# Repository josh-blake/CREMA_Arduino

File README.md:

CREMA
=====

ControlleR for Espresso MAchines (http://josh.to/crema)

This entire project (including hardware and software) is distrubuted under the Creative Commons Attribution-NonCommercial-ShareAlike 3.0 Unported License.
http://creativecommons.org/licenses/by-nc-sa/3.0/deed.en_US

Please contact crema at josh dot to if you have any specific questions or would like to contribute to this project.

Enjoy the espresso.

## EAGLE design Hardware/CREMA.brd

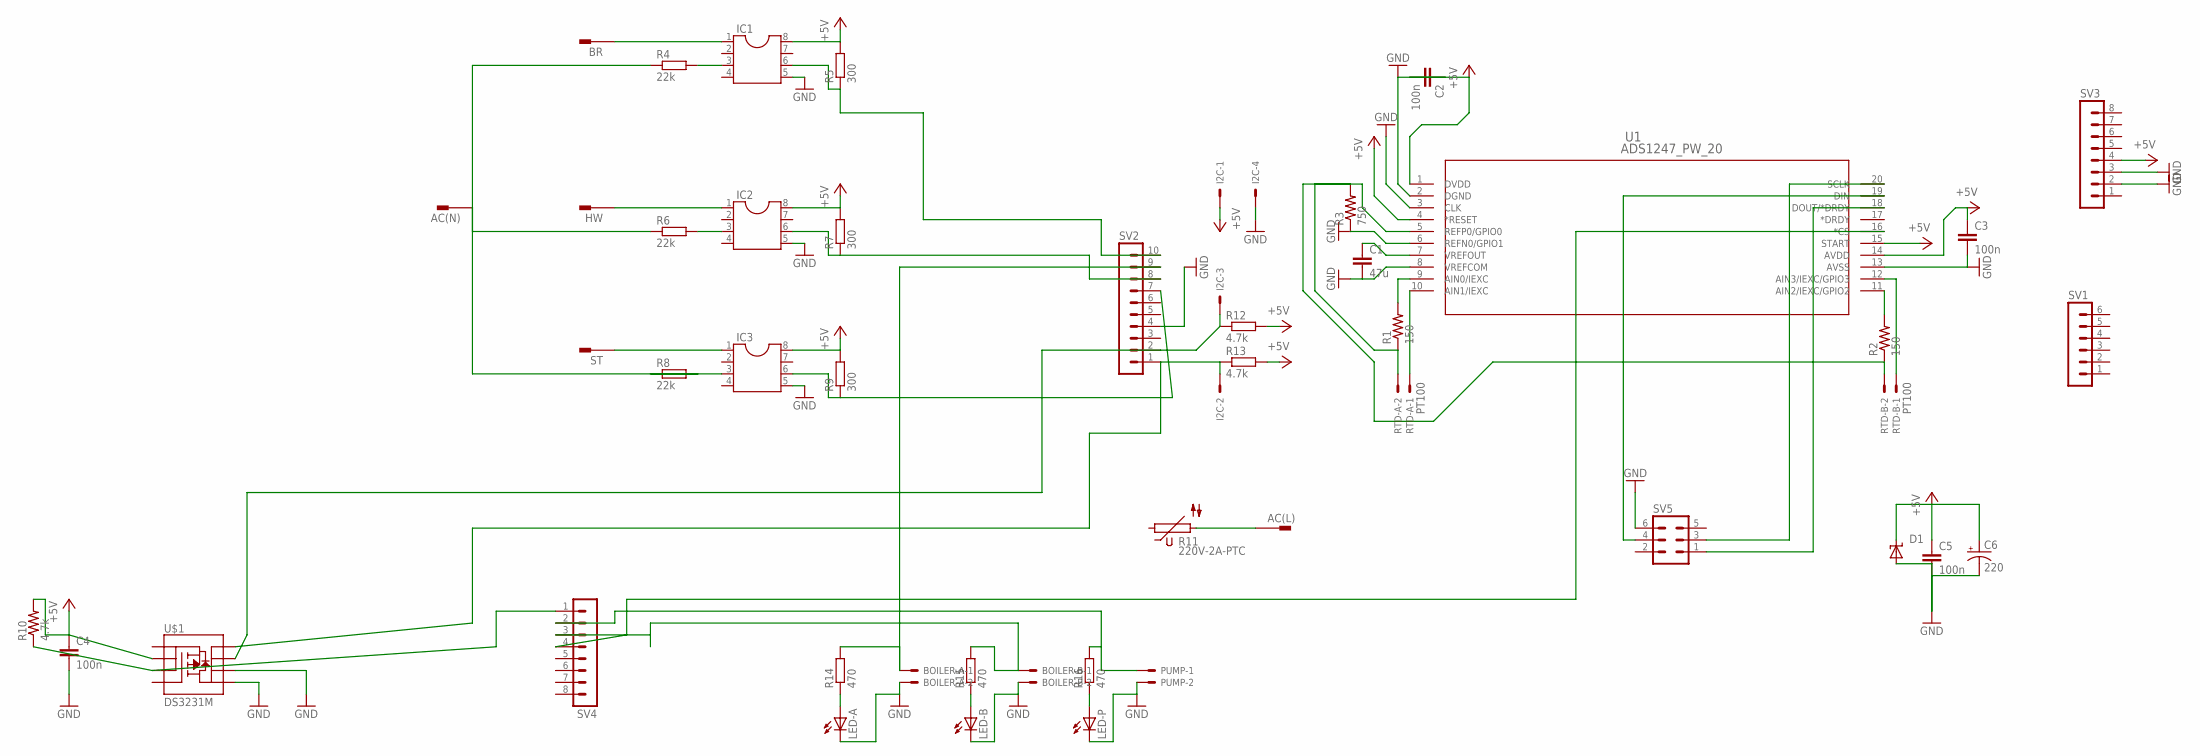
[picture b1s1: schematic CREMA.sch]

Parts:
AC(L): PIN262409-1; 62409-1
AC(N): PIN262409-1; 62409-1
BOILER-A: C-GRID-02-70543; 70543-02
BOILER-B: C-GRID-02-70543; 70543-02
BR: PIN262409-1; 62409-1
C1: 47u; C0805
C2, C3, C4, C5: 100n; C0805
C6: 220; D/7343-31W
D1: SUPPRESSOR-SMBJ; SMBJ
HW: PIN262409-1; 62409-1
I2C: C-GRID-04-70543; 70543-04
IC1, IC2, IC3: DIL8; DIL08
LED-A: LEDSML0603; SML0603
LED-B: LEDSML0603; SML0603
LED-P: LEDSML0603; SML0603
PUMP: C-GRID-02-70543; 70543-02
R1, R2: 150; R0603
R3: 750; R0603
R4, R6, R8: 22k; R1206
R5, R7, R9: 300; R1206
R10, R12, R13: 4.7k; R0603
R11: 220V-2A-PTC; S20K11
R14, R15, R16: 470; R0603
RTD-A: PT100; 70543-02
RTD-B: PT100; 70543-02
ST: PIN262409-1; 62409-1
SV1: MA06-1
SV2: MA10-1
SV3, SV4: MA08-1
SV5: MA03-2
U1: ADS1247_PW_20; PW20
U$1: DS3231M; SO08

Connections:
+5V: C2.2, C3.1, C4.1, C5.1, C6.+, D1.C, I2C.1, IC1.8, IC2.8, IC3.8, R5.2, R7.2, R9.2, R10.2, R12.2, R13.2, SV3.4, U1.1 (DVDD), U1.4 (*RESET), U1.14 (AVDD), U1.15 (START), U$1.2 (S)
GND: BOILER-A.2, BOILER-B.2, C1.2, C2.1, C3.2, C4.2, C5.2, C6.-, D1.A, I2C.4, IC1.5, IC2.5, IC3.5, LED-A.C, LED-B.C, LED-P.C, PUMP.2, R3.1, SV2.4, SV3.2, SV3.3, SV5.6, U1.2 (DGND), U1.3 (CLK), U1.6 (REFN0/GPIO1), U1.8 (VREFCOM), U1.13 (AVSS), U$1.5 (D), U$1.6 (D)
unnamed: I2C.3, R12.1, SV2.2, U$1.7 (D)
unnamed: C1.1, U1.7 (VREFOUT)
unnamed: RTD-A.1, U1.10 (AIN1/IEXC)
unnamed: R1.1, R2.1, R3.2, RTD-A.2, RTD-B.2, U1.5 (REFP0/GPIO0)
unnamed: R1.2, U1.9 (AIN0/IEXC)
unnamed: R2.2, U1.11 (AIN2/IEXC/GPIO2)
unnamed: RTD-B.1, U1.12 (AIN3/IEXC/GPIO3)
unnamed: BR.A1, BR.A2, IC1.1
unnamed: IC1.3, R4.2
unnamed: IC1.6, R5.1, SV2.10
unnamed: HW.A1, HW.A2, IC2.1
unnamed: IC2.3, R6.2
unnamed: IC2.6, R7.1, SV2.8
unnamed: IC3.1, ST.A1, ST.A2
unnamed: IC3.3, R8.1
unnamed: IC3.6, R9.1, SV2.7
unnamed: AC(N).A1, AC(N).A2, R4.1, R6.1, R8.2
unnamed: R10.1, SV4.1, U$1.3 (S)
unnamed: AC(L).A1, AC(L).A2, R11.2
unnamed: LED-A.A, R14.1
unnamed: SV4.4, U1.16 (*CS)
unnamed: SV5.1, U1.18 (DOUT/*DRDY)
unnamed: SV5.3, U1.20 (SCLK)
unnamed: SV5.4, U1.19 (DIN)
unnamed: I2C.2, R13.1, SV2.1, U$1.8 (D)
unnamed: BOILER-A.1, R14.2, SV2.9
unnamed: BOILER-B.1, R15.2, SV4.3
unnamed: PUMP.1, R16.2, SV4.2
unnamed: LED-B.A, R15.1
unnamed: LED-P.A, R16.1

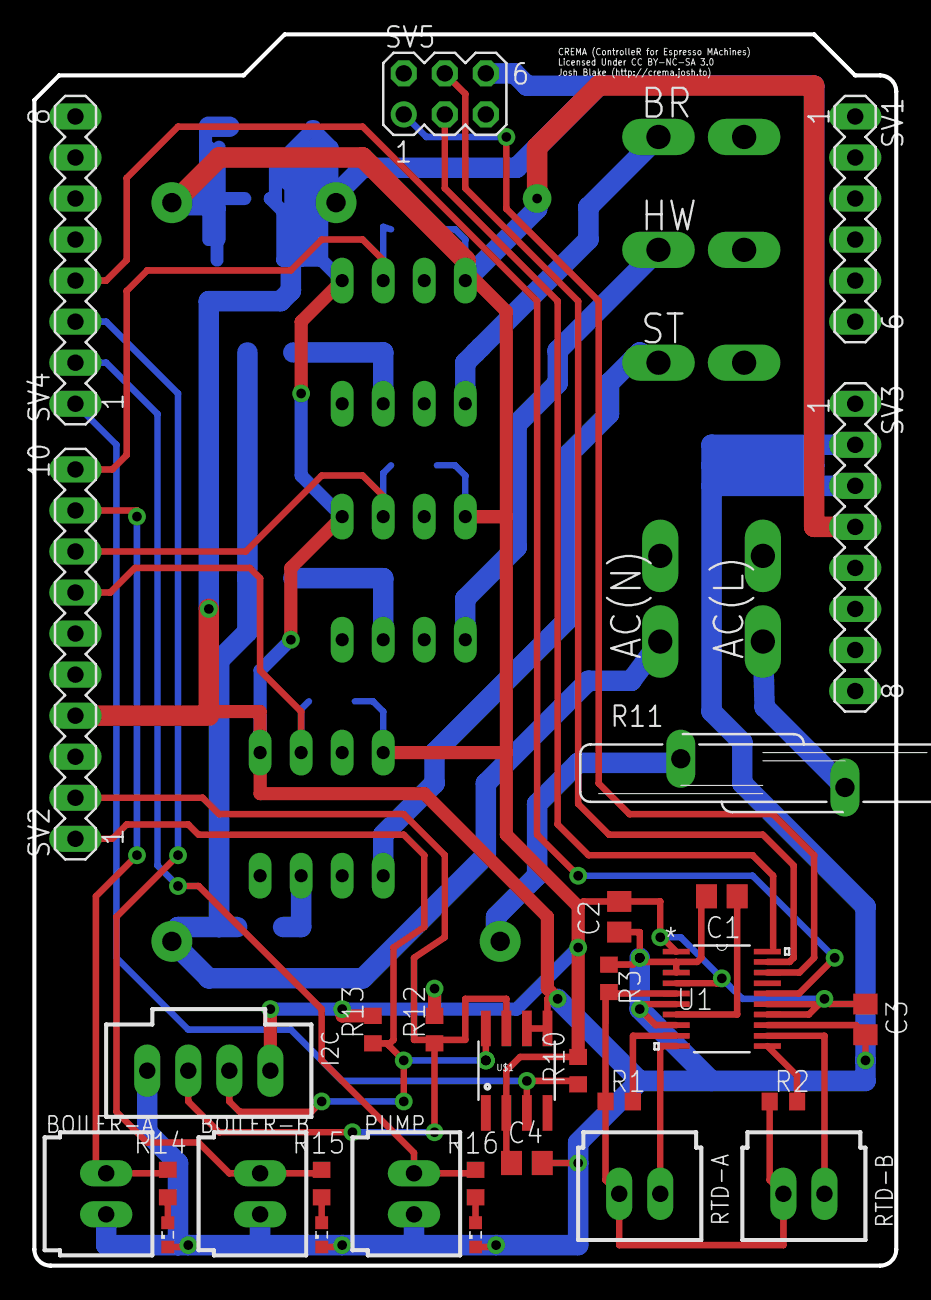
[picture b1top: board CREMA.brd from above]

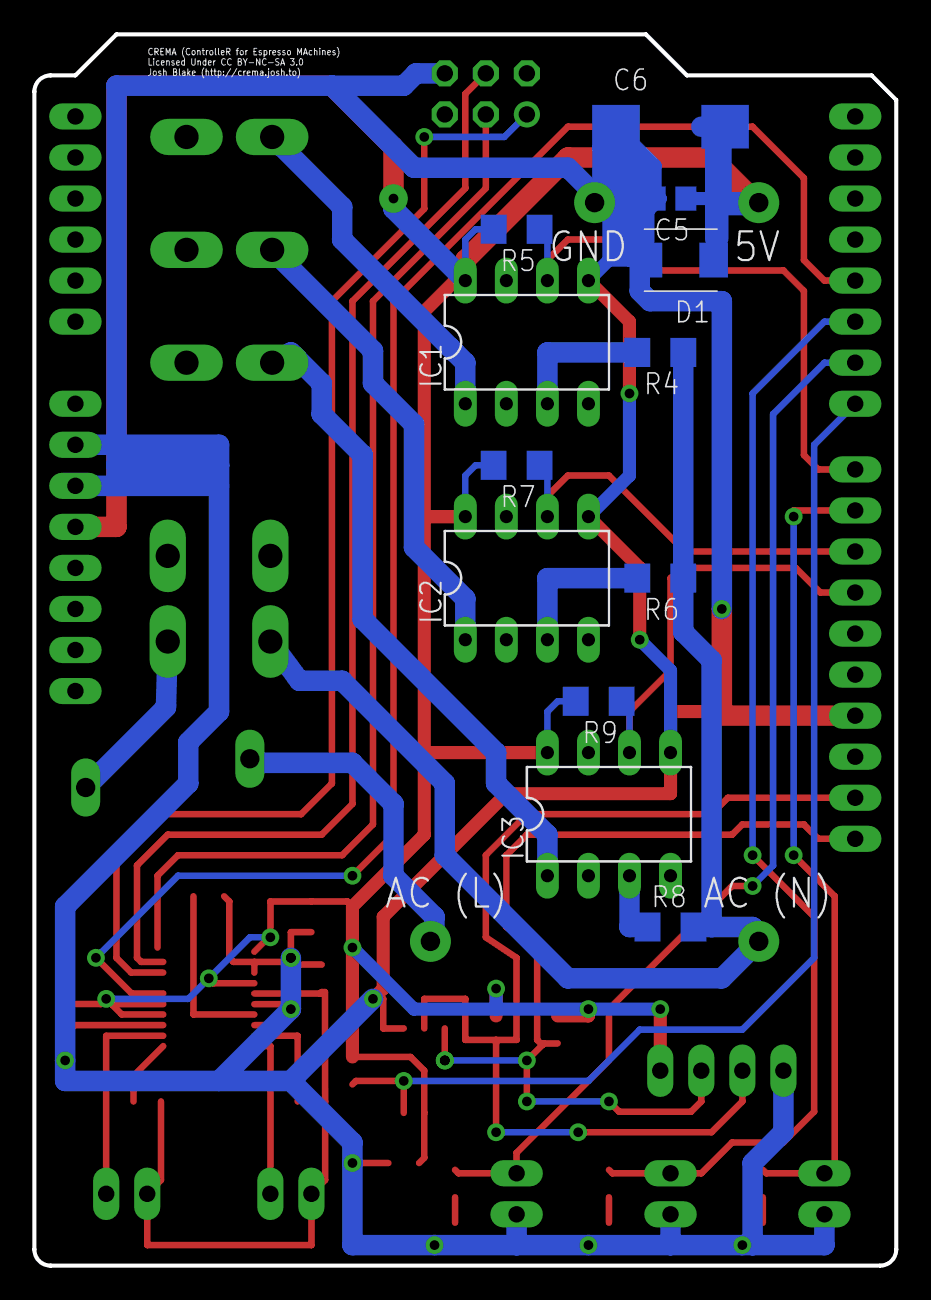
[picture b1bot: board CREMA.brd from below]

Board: 2 copper layers, 53.3 x 76.2 mm, 47 parts (12 on the bottom side), 32 nets.

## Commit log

2013-07-21 First Public Revision of the CREMA Firmware
2013-10-16 First Public Release of Firmware and Hardware.
2013-10-18 Got rid of .DS_Store
2013-10-18 Updated CC License in Firmware Files

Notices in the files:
Hardware/CREMA.brd:
Licensed Under CC BY-NC-SA 3.0
parts and their libraries:
SparkFun-DiscreteSemi: Licensing: CC v3.0 Share-Alike You are welcome to use this library for commercial purposes.
